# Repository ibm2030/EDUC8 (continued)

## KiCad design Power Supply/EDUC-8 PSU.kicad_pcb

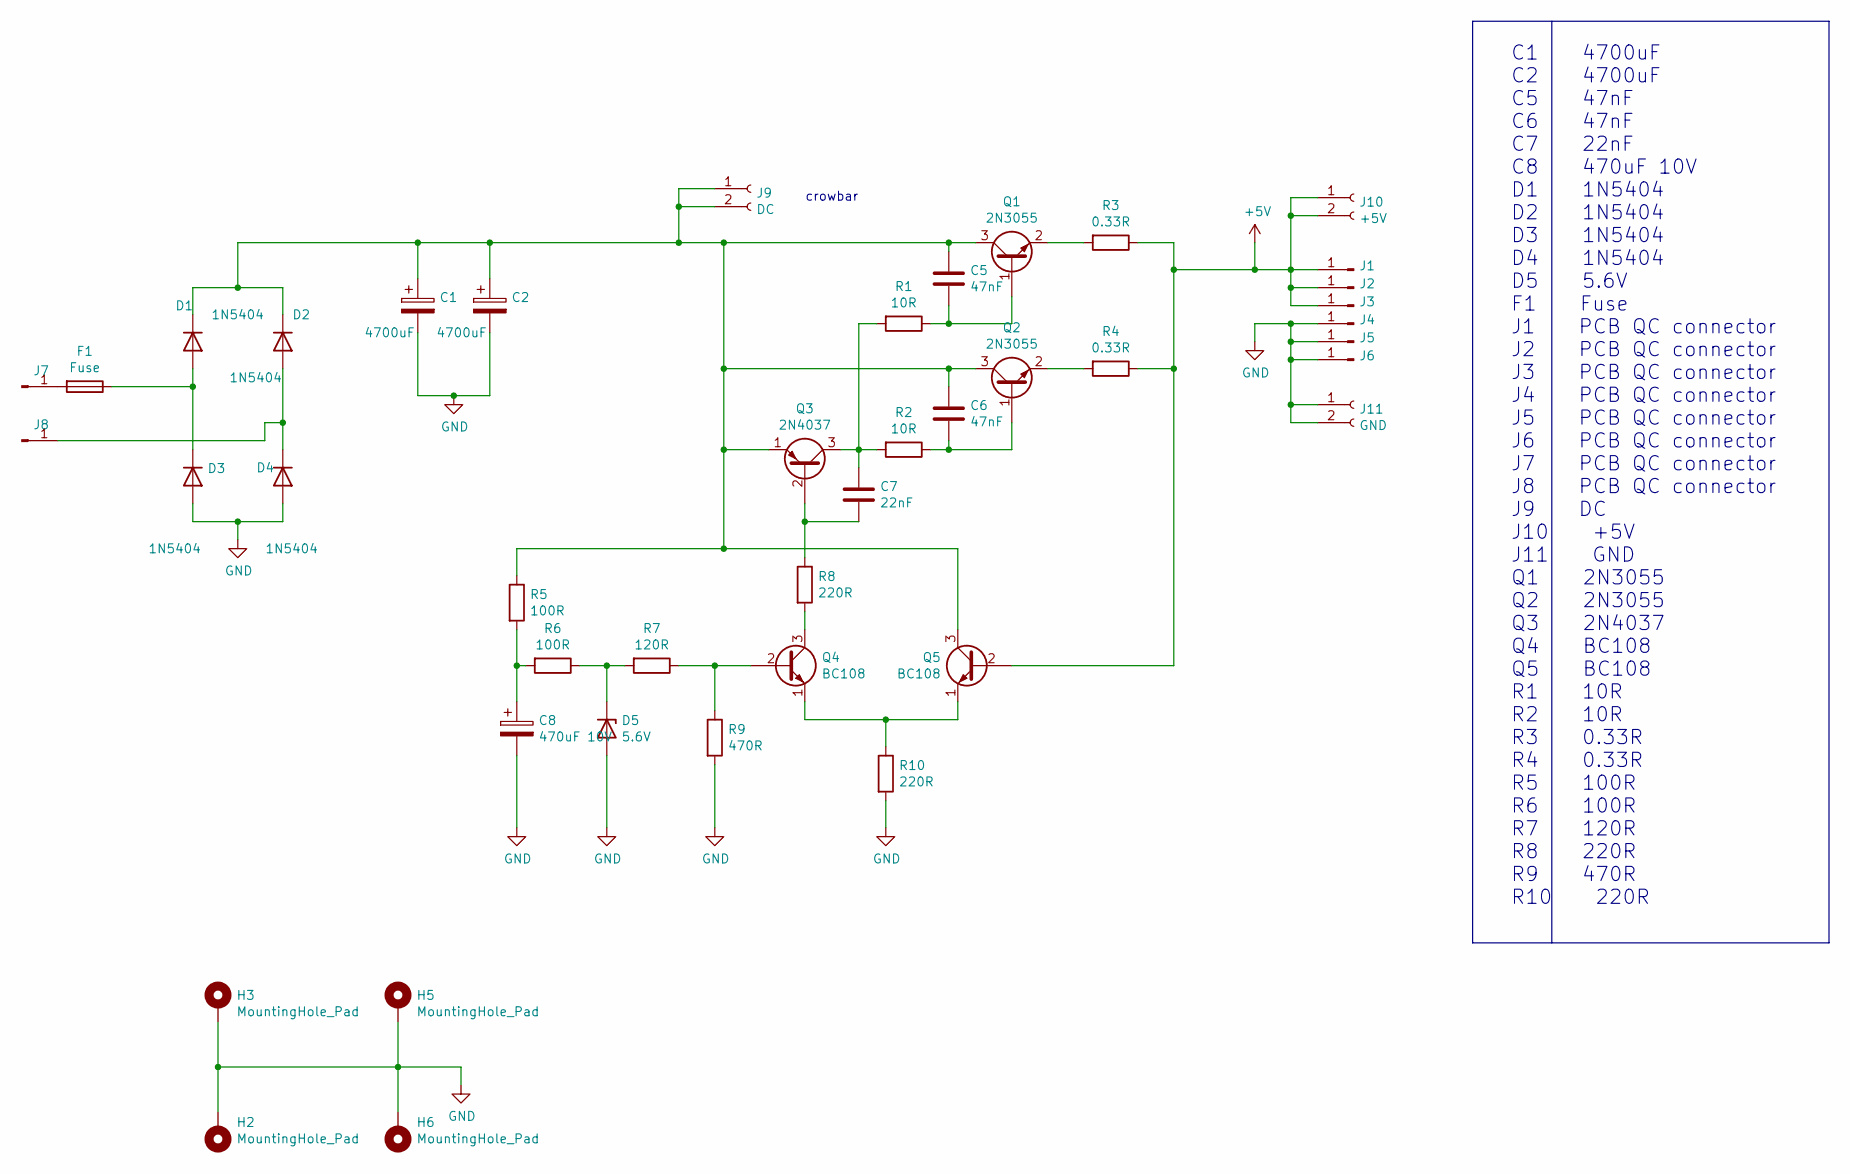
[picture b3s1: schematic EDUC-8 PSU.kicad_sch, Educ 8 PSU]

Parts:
C1, C2: 4700uF; CP_Radial_D25.0mm_P10.00mm_SnapIn
C5, C6: 47nF; C_Rect_L7.2mm_W3.5mm_P5.00mm_FKS2_FKP2_MKS2_MKP2
C7: 22nF; C_Rect_L7.0mm_W6.0mm_P5.00mm
C8: 470uF 10V; CP_Radial_D12.5mm_P5.00mm
D1, D2, D3, D4: 1N5404; D_DO-201AD_P15.24mm_Horizontal
D5: 5.6V; D_DO-41_SOD81_P10.16mm_Horizontal
F1: Fuse; Fuseholder_Cylinder-6.3x32mm_Schurter_0031-8002_Horizontal_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
H2, H3, H5, H6: MountingHole_Pad; MountingHole_4.3mm_M4_Pad_Via
J1, J2, J3, J4, J5, J6, J7, J8: Conn_01x01_Male; QC_Terminal_PCB_W6.3mm_P5mm_
J9: DC; PinSocket_2x01_P2.54mm_Vertical
J10: +5V; PinSocket_2x01_P2.54mm_Vertical
J11: GND; PinSocket_2x01_P2.54mm_Vertical
Q1, Q2: 2N3055; TO-3
Q3: 2N4037; TO-39-3
Q4, Q5: BC108; TO-18-3
R1, R2: 10R; R_Axial_DIN0411_L9.9mm_D3.6mm_P15.24mm_Horizontal
R3, R4: 0.33R; R_Axial_Power_L25.0mm_W9.0mm_P30.48mm
R5, R6: 100R; R_Axial_DIN0309_L9.0mm_D3.2mm_P12.70mm_Horizontal
R7: 120R; R_Axial_DIN0309_L9.0mm_D3.2mm_P12.70mm_Horizontal
R8, R10: 220R; R_Axial_DIN0309_L9.0mm_D3.2mm_P12.70mm_Horizontal
R9: 470R; R_Axial_DIN0309_L9.0mm_D3.2mm_P12.70mm_Horizontal

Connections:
+5V: J1.1, J2.1, J3.1, J10.1, J10.2, Q5.2 (B), R3.1, R4.1
GND: C1.2, C2.2, C8.2, D3.2 (A), D4.2 (A), D5.2 (A), H2.1, H3.1, H5.1, H6.1, J4.1, J5.1, J6.1, J11.1, J11.2, R9.2, R10.2
unnamed: C1.1, C2.1, C5.1, C6.1, D1.1 (K), D2.1 (K), J9.1, J9.2, Q1.3 (C), Q2.3 (C), Q3.1 (E), Q5.3 (C), R5.1
unnamed: C5.2, Q1.1 (B), R1.1
unnamed: C6.2, Q2.1 (B), R2.1
unnamed: C7.1, Q3.3 (C), R1.2, R2.2
unnamed: C7.2, Q3.2 (B), R8.1
unnamed: C8.1, R5.2, R6.2
unnamed: D1.2 (A), D3.1 (K), F1.1
unnamed: D2.2 (A), D4.1 (K), J8.1
unnamed: D5.1 (K), R6.1, R7.2
unnamed: F1.2, J7.1
unnamed: Q1.2 (E), R3.2
unnamed: Q2.2 (E), R4.2
unnamed: Q4.1 (E), Q5.1 (E), R10.1
unnamed: Q4.2 (B), R7.1, R9.1
unnamed: Q4.3 (C), R8.2

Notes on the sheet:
C1 4700uF C2 4700uF C5 47nF C6 47nF C7 22nF C8 470uF 10V D1 1N5404 D2 1N5404 D3 1N5404 D4 1N5404 D5 5.6V F1 Fuse J1 PCB QC connector J2 PCB QC connector J3 PCB QC connector J4 PCB QC connector J5 PCB QC connector J6 PCB QC connector J7 PCB QC connector J8 PCB QC connector J9 DC J10 +5V J11 GND Q1 2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
crowbar

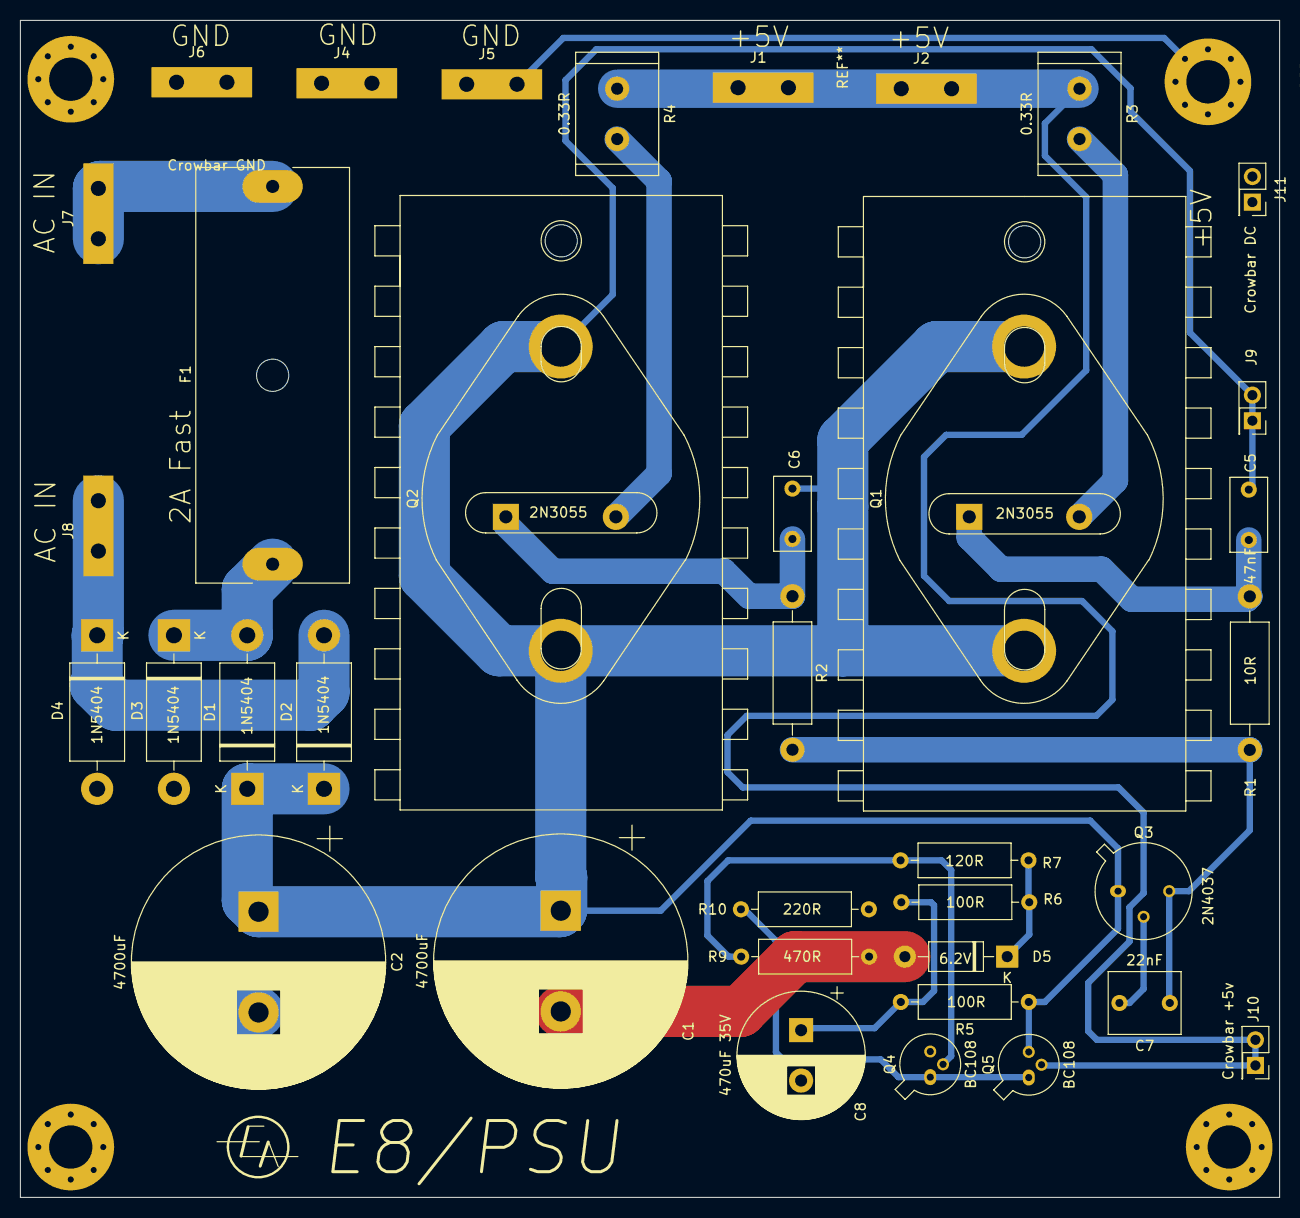
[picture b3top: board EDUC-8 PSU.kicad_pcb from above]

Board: 2 copper layers, 125.0 x 116.8 mm, 40 parts (0 on the bottom side), 16 nets.

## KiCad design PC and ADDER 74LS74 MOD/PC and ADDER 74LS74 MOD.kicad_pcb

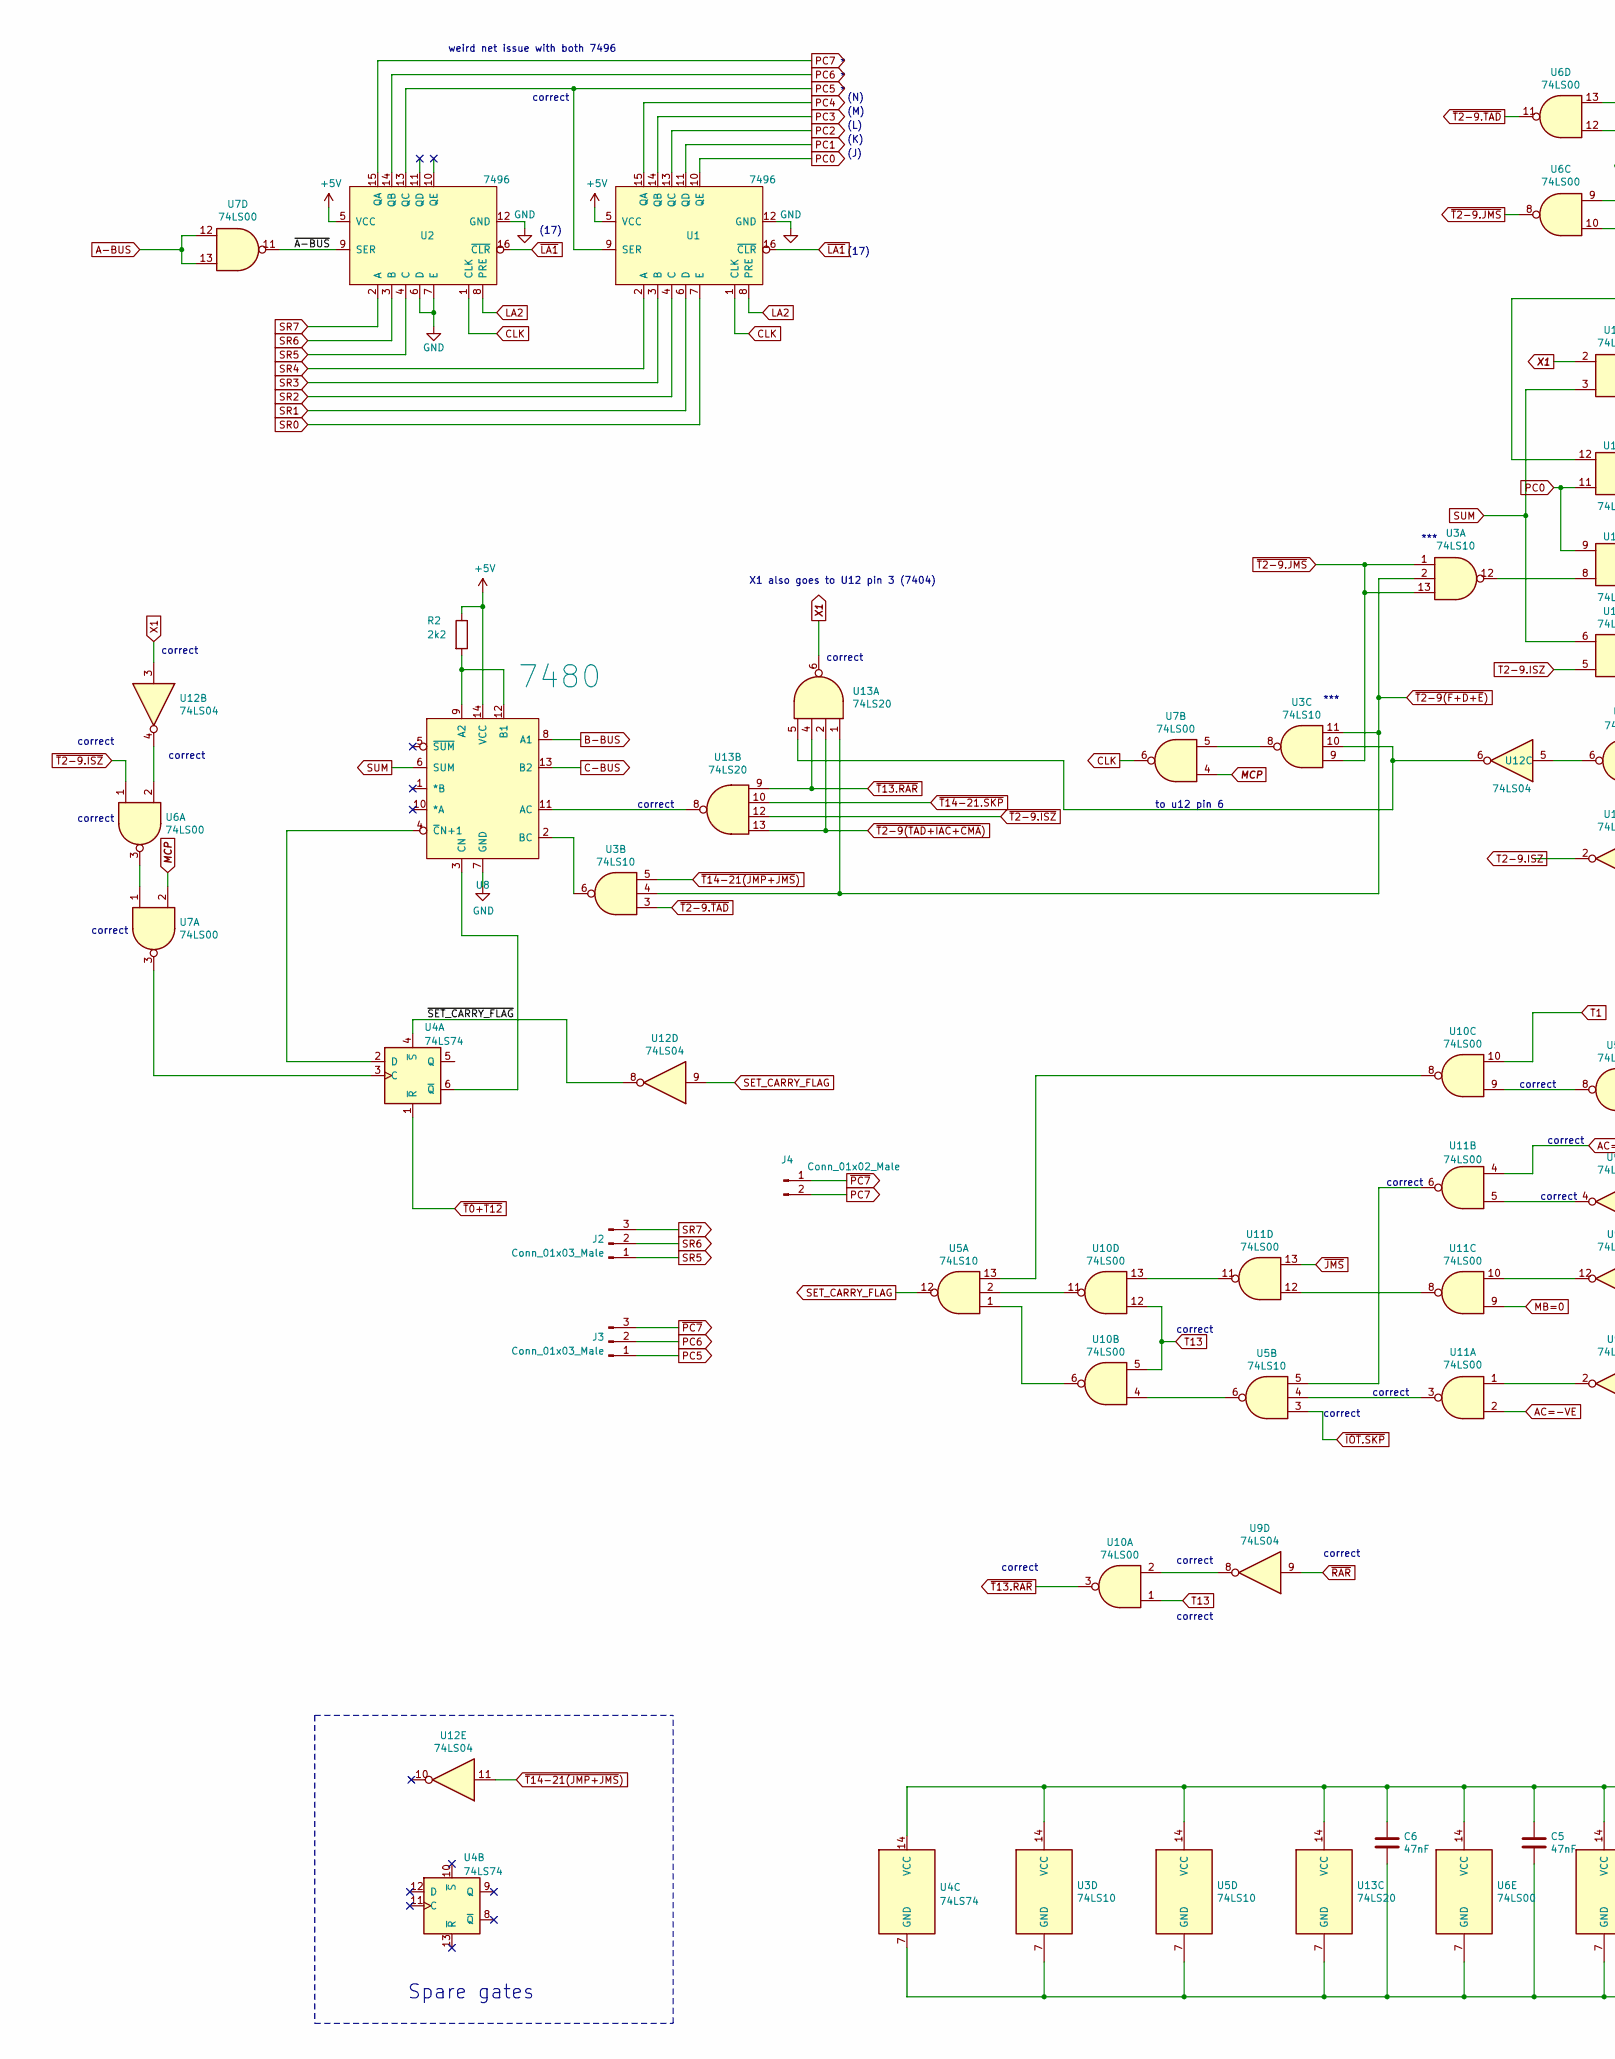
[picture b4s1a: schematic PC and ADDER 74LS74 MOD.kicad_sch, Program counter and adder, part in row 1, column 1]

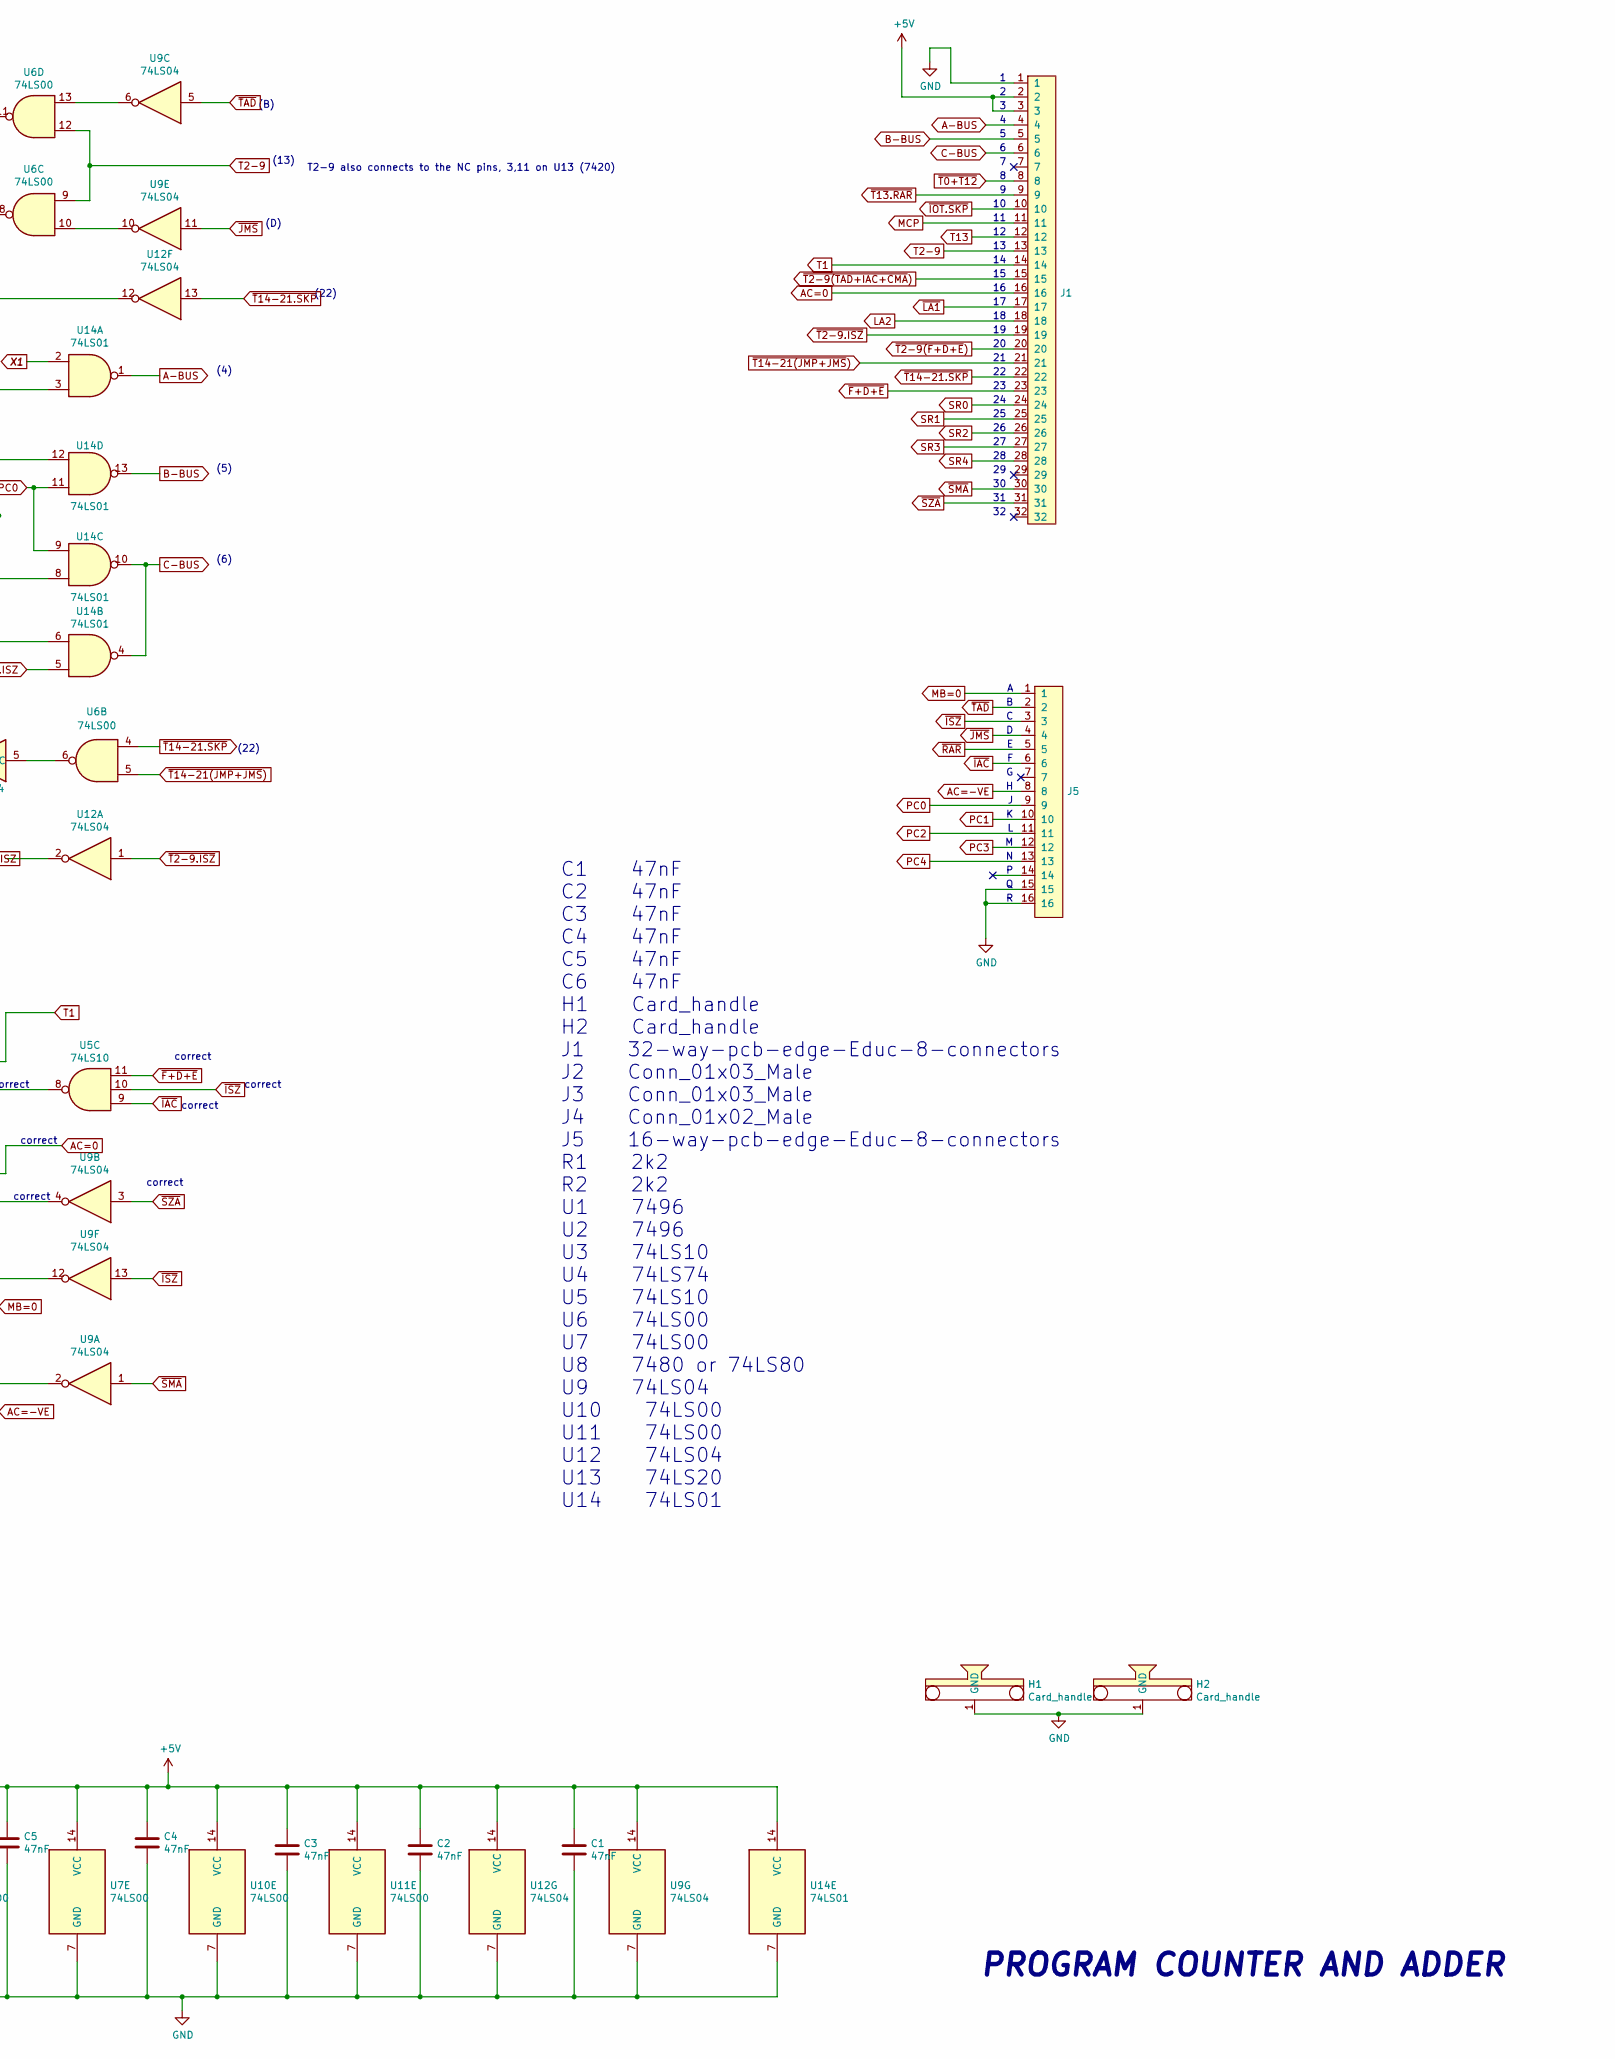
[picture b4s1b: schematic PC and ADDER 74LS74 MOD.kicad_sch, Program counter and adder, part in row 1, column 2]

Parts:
C1, C2, C3, C4, C5, C6: 47nF; C_Disc_D7.5mm_W5.0mm_P7.50mm
H1, H2: Card_handle
J1: 32-way-pcb-edge-Educ-8-connectors; PCB_32pin
J2, J3: Conn_01x03_Male; JST_XH_B3B-XH-AM_1x03_P2.50mm_Vertical
J4: Conn_01x02_Male; JST_XH_B2B-XH-AM_1x02_P2.50mm_Vertical
J5: 16-way-pcb-edge-Educ-8-connectors; PCB_16pin
R2: 2k2; R_Axial_DIN0207_L6.3mm_D2.5mm_P10.16mm_Horizontal
U1, U2: 7496; DIP-16_W7.62mm
U3: 74LS10
U4: 74LS74; DIP-14_W7.62mm_LongPads
U5: 74LS10; DIP-14_W7.62mm
U6, U7: 74LS00; DIP-14_W7.62mm
U8: 7480; DIP-14_W7.62mm
U9: 74LS04
U10, U11: 74LS00
U12: 74LS04; DIP-14_W7.62mm
U13: 74LS20
U14: 74LS01

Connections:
+5V: C1.1, C2.1, C3.1, C4.1, C5.1, C6.1, J1.2, J1.3, R2.1, U1.5 (VCC), U2.5 (VCC), U3.14 (VCC), U4.14 (VCC), U5.14 (VCC), U6.14 (VCC), U7.14 (VCC), U8.14 (VCC), U9.14 (VCC), U10.14 (VCC), U11.14 (VCC), U12.14 (VCC), U13.14 (VCC), U14.14 (VCC); also elsewhere on the board
/~A-BUS: U2.9 (SER), U7.11
/~SET_CARRY_FLAG: U4.4 (~S), U12.8
A-BUS: J1.4, U7.12, U7.13, U14.1
AC=0: J1.16, U11.4
AC=-VE: J5.8, U11.2
B-BUS: J1.5, U8.8 (A1), U14.13
C-BUS: J1.6, U8.13 (B2), U14.4, U14.10
CLK: U1.1 (CLK), U2.1 (CLK), U7.6
GND: C1.2, C2.2, C3.2, C4.2, C5.2, C6.2, H1.1 (GND), H2.1 (GND), J1.1, J5.15, J5.16, U1.12 (GND), U2.6 (D), U2.7 (E), U2.12 (GND), U3.7 (GND), U4.7 (GND), U5.7 (GND), U6.7 (GND), U7.7 (GND), U8.7 (GND), U9.7 (GND), U10.7 (GND), U11.7 (GND), U12.7 (GND), U13.7 (GND), U14.7 (GND); also elsewhere on the board
LA2: J1.18, U1.8 (PRE), U2.8 (PRE)
MB=0: J5.1, U11.9
MCP: J1.11, U7.2, U7.4
unnamed: U3.8, U7.5
unnamed: U4.3 (C), U7.3
unnamed: U4.2 (D), U8.4 (~CN+1)
unnamed: U4.6 (~Q), U8.3 (CN)
unnamed: U6.3, U7.1
unnamed: U6.10, U9.10
unnamed: U6.13, U9.6
unnamed: R2.2, U8.9 (A2), U8.12 (B1)
unnamed: U8.11 (AC), U13.8
unnamed: U3.6, U8.2 (BC)
unnamed: U9.8, U10.2
unnamed: U5.6, U10.4
unnamed: U5.1, U10.6
unnamed: U5.13, U10.8
unnamed: U5.8, U10.9
unnamed: U5.2, U10.11
unnamed: U10.13, U11.11
unnamed: U9.2, U11.1
unnamed: U5.4, U11.3
unnamed: U9.4, U11.5
unnamed: U5.5, U11.6
unnamed: U9.12, U11.10
unnamed: U11.8, U11.12
unnamed: U6.2, U12.4
unnamed: U6.6, U12.5
unnamed: U3.10, U12.6, U13.5
unnamed: U12.12, U14.12
unnamed: U3.12, U14.8
PC0: J5.9, U1.10 (QE), U14.9, U14.11
PC1: J5.10, U1.11 (QD)
PC2: J5.11, U1.13 (QC)
PC3: J5.12, U1.14 (QB)
PC4: J5.13, U1.15 (QA)
PC5: J3.1, U1.9 (SER), U2.13 (QC)
PC6: J3.2, U2.14 (QB)
PC7: J4.2, U2.15 (QA)
SET_CARRY_FLAG: U5.12, U12.9
SR0: J1.24, U1.7 (E)
SR1: J1.25, U1.6 (D)
SR2: J1.26, U1.4 (C)
SR3: J1.27, U1.3 (B)
SR4: J1.28, U1.2 (A)
SR5: J2.1, U2.4 (C)
SR6: J2.2, U2.3 (B)
SR7: J2.3, U2.2 (A)
SUM: U8.6 (SUM), U14.3, U14.6
T1: J1.14, U10.10
T2-9: J1.13, U6.9, U6.12
T2-9.ISZ: U12.2, U14.5
T13: J1.12, U10.1, U10.5, U10.12
X1: U12.3, U13.6, U14.2
~F+D+E: J1.23, U5.11
~IAC: J5.6, U5.9
~IOT.SKP: J1.10, U5.3
~ISZ: J5.3, U5.10, U9.13
~JMS: J5.4, U9.11, U11.13
~LA1: J1.17, U1.16 (~CLR), U2.16 (~CLR)
~PC7: J3.3, J4.1
~RAR: J5.5, U9.9
~SMA: J1.30, U9.1
~SZA: J1.31, U9.3
~T0+T12: J1.8, U4.1 (~R)
~T2-9(F+D+E): J1.20, U3.2, U3.4, U3.11, U13.1
~T2-9(TAD+IAC+CMA): J1.15, U13.2, U13.13
~T2-9.ISZ: J1.19, U6.1, U12.1, U13.12
~T2-9.JMS: U3.1, U3.9, U3.13, U6.8
~T2-9.TAD: U3.3, U6.11
~T13.RAR: J1.9, U10.3, U13.4, U13.9
~T14-21(JMP+JMS): J1.21, U3.5, U6.5, U12.11
~T14-21.SKP: J1.22, U6.4, U12.13, U13.10
~TAD: J5.2, U9.5

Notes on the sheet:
correct
(M)
(B)
***
(L)
(22)
(17)
(13)
(6)
(5)
(K)
X1 also goes to U12 pin 3 (7404)
(J)
(N)
C1 47nF C2 47nF C3 47nF C4 47nF C5 47nF C6 47nF H1 Card_handle H2 Card_handle J1 32-way-pcb-edge-Educ-8-connectors J2 Conn_01x03_Male J3 Conn_01x03_Male J4 Conn_01x02_Male J5 16-way-pcb-edge-Educ-8-connectors R1 2k2 R2 2k2 U1 7496 U2 7496 U3 74LS10 U4 74LS74 U5 74LS10 U6 74LS00 U7 74LS00 U8 7480 or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
(4)
PROGRAM COUNTER AND ADDER
T2-9 also connects to the NC pins, 3,11 on U13 (7420)
weird net issue with both 7496
(D)
Spare gates
to u12 pin 6

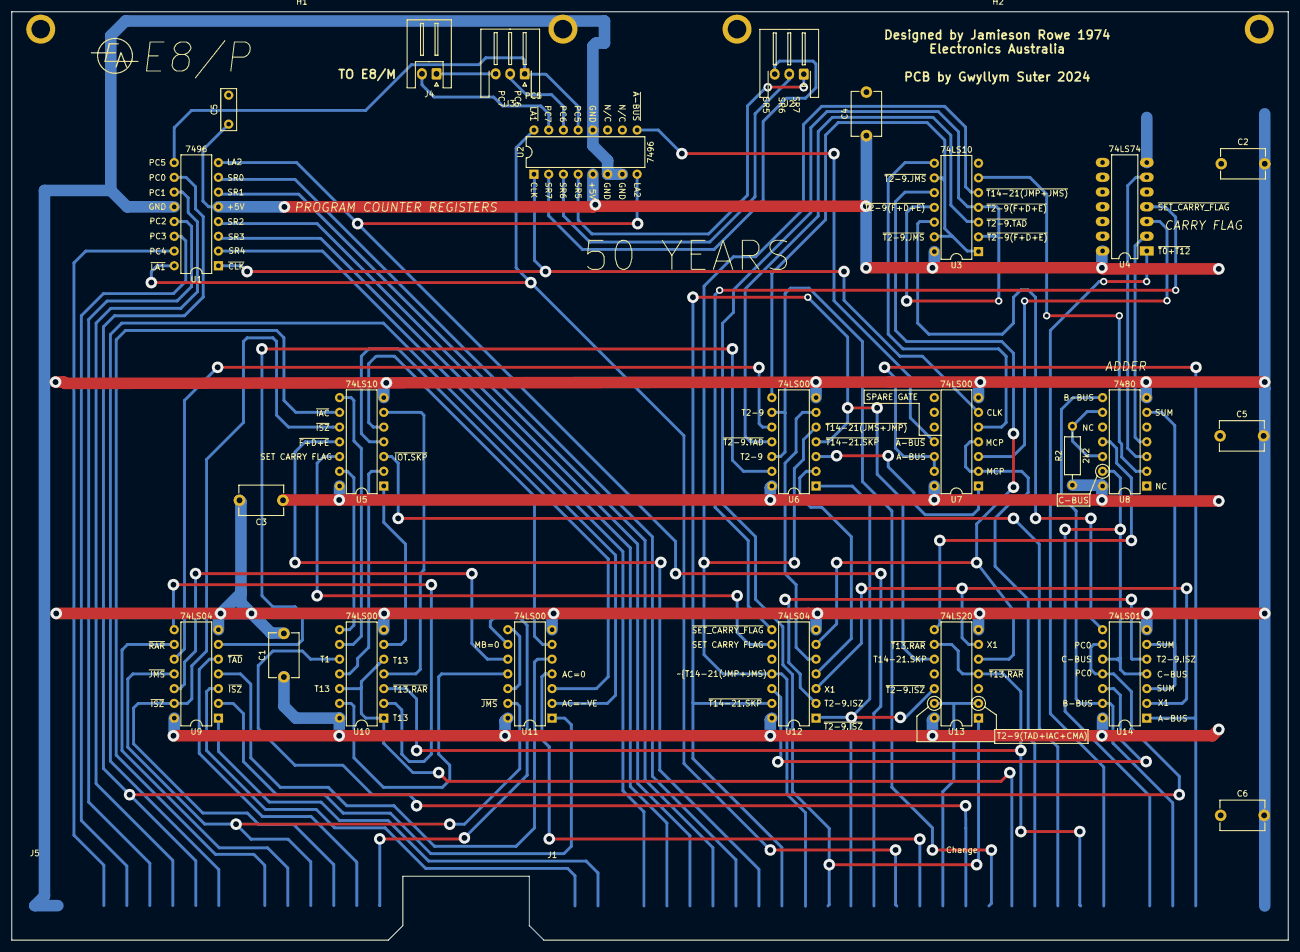
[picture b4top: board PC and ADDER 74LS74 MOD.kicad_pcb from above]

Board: 2 copper layers, 220.0 x 160.0 mm, 29 parts (0 on the bottom side), 84 nets.

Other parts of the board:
C5#2: 47nF; C_Disc_D7.5mm_W5.0mm_P7.50mm

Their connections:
+5V: C5#2.1; also elsewhere on the board
GND: C5#2.2; also elsewhere on the board
